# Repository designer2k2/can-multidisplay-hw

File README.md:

# can-multidisplay-hw
Displaying and measuring automotive related values, with CAN, GPS and more

Software: https://github.com/designer2k2/can-multidisplay

## Features:

* Teensy 4 Microcontroller https://www.pjrc.com/store/teensy40.html
* 12V -> 5V Power supply with TPS2113A voltage selector
* 3,3V Power supply
* RTC battery to support Teensy
* SD card slot, with flex cable to Teensy
* WS2812 level shifter 74AHCT1G125
* GPS serial port
* CAN transceiver SN65HVD232 with selectable 120Ohm resistor
* RS232 level shifter MAX3232
* MPU-6050  Six-Axis (Gyro + Accelerometer)
* I2C Levelshifter to 5V
* TMP75AIDR I2C Temperature sensor
* 4 channel 12Bit ADC ADS1015IDGS
* 6 protected inputs
* SSD1351 OLED  Interface
* ILI9341 + XPT2046 Touch display Interface

PCB is made in KiCad and parts selected to have it produced by JLCPCB

## Images:

PCB Backside:

3D Rendering with Display, GPS and RGB LED:

Display running:

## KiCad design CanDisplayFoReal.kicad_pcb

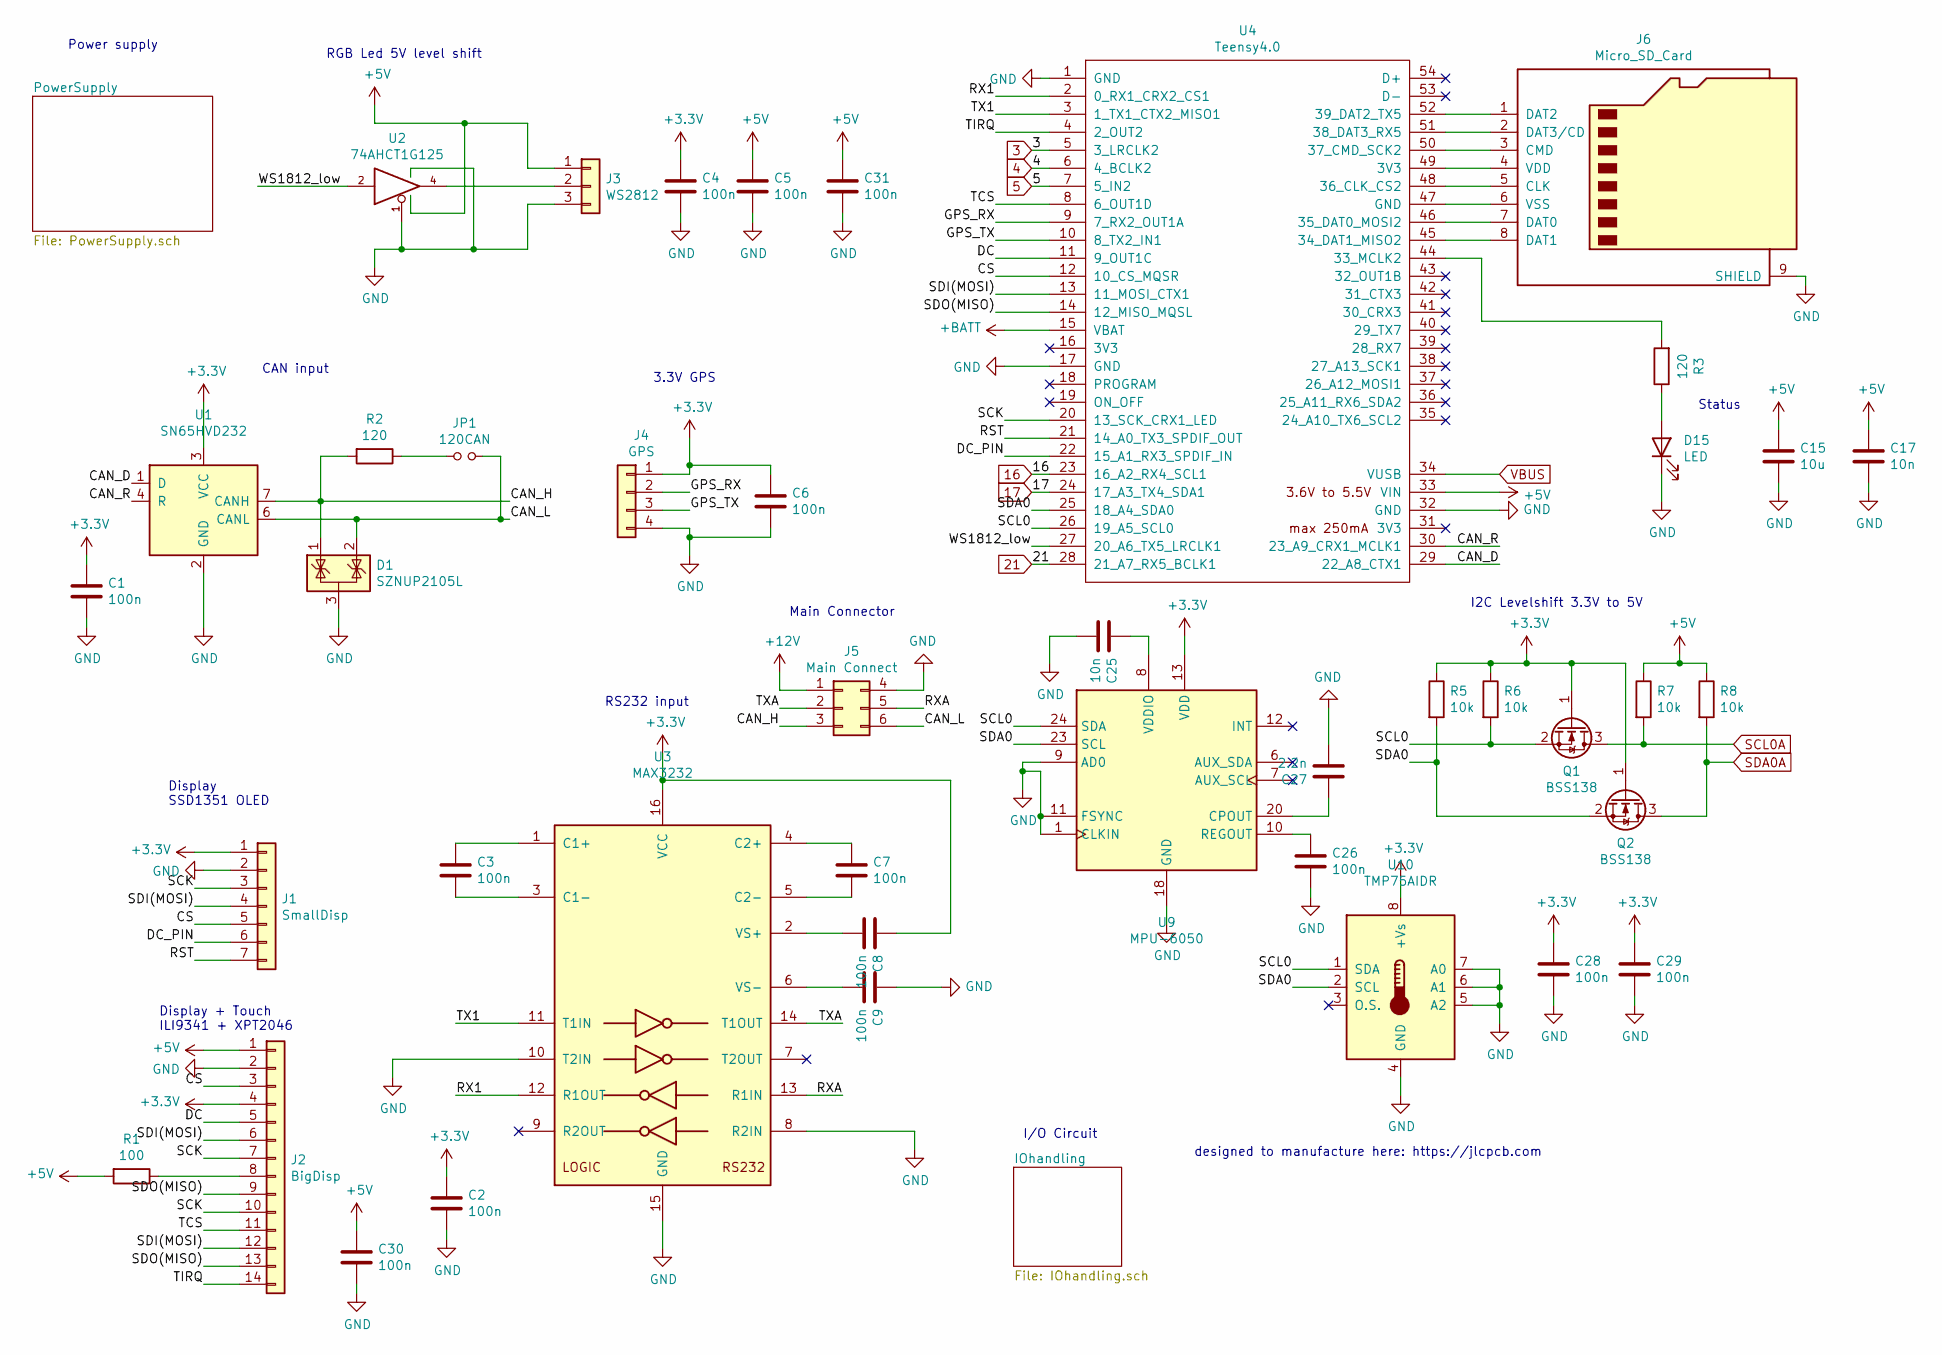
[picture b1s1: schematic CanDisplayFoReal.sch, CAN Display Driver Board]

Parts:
C1, C2, C3, C4, C5, C6, C7, C8, C9, C26, C28, C29, C30, C31: 100n; C_0603_1608Metric; JLCPCB C14663
C15: 10u; C_1206_3216Metric; JLCPCB C13585
C17, C25: 10n; C_0805_2012Metric; JLCPCB C1710
C27: 2.2n; C_0805_2012Metric; JLCPCB C28260
D1: SZNUP2105L; SOT-23; JLCPCB C233494
D15: LED; LED_0603_1608Metric; JLCPCB C2286
J1: SmallDisp; PinHeader_1x07_P2.54mm_Vertical
J2: BigDisp; PinHeader_1x14_P2.54mm_Vertical
J3: WS2812; PinHeader_1x03_P2.54mm_Vertical
J4: GPS; PinHeader_1x04_P2.54mm_Vertical
J5: Main Connect; Molex_Micro-Fit_3.0_43045-0612_2x03_P3.00mm_Vertical
J6: Micro_SD_Card; microSD_HC_Wuerth_693072010801
JP1: 120CAN; PinHeader_1x02_P2.54mm_Vertical
Q1, Q2: BSS138; SOT-23; JLCPCB C52895
R1: 100; R_0603_1608Metric; JLCPCB C22775
R2, R3: 120; R_0603_1608Metric; JLCPCB C22787
R5, R6, R7, R8: 10k; R_0603_1608Metric; JLCPCB C25804
U1: SN65HVD232; SOIC-8_3.9x4.9mm_P1.27mm; JLCPCB C30530
U2: 74AHCT1G125; SOT-23-5; JLCPCB C12494
U3: MAX3232; TSSOP-16_4.4x5mm_P0.65mm; JLCPCB C19767
U4: Teensy4.0; Teensy40_SMT
U9: MPU-6050; InvenSense_QFN-24_4x4mm_P0.5mm; JLCPCB C24112
U10: TMP75AIDR; SOIC-8_3.9x4.9mm_P1.27mm; JLCPCB C30389

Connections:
3: U4.5 (3_LRCLK2); also elsewhere on the board
4: U4.6 (4_BCLK2); also elsewhere on the board
5: U4.7 (5_IN2); also elsewhere on the board
16: U4.23 (16_A2_RX4_SCL1); also elsewhere on the board
17: U4.24 (17_A3_TX4_SDA1); also elsewhere on the board
21: U4.28 (21_A7_RX5_BCLK1); also elsewhere on the board
+3V3: C1.1, C2.1, C4.1, C6.1, C8.1, C28.1, C29.1, J1.1, J2.4, J4.1, Q1.1 (G), Q2.1 (G), R5.1, R6.1, U1.3 (VCC), U3.16 (VCC), U9.13 (VDD), U10.8 (+Vs); also elsewhere on the board
+5V: C5.1, C15.1, C17.1, C30.1, C31.1, J2.1, J3.1, R1.2, R7.1, R8.1, U2.5 (VCC), U4.33 (VIN); also elsewhere on the board
+12V: J5.1; also elsewhere on the board
+BATT: U4.15 (VBAT); also elsewhere on the board
/CAN_D: U1.1 (D), U4.29 (22_A8_CTX1)
/CAN_H: D1.1 (K), J5.3, R2.2, U1.7 (CANH)
/CAN_L: D1.2 (K), J5.6, JP1.2, U1.6 (CANL)
/CAN_R: U1.4 (R), U4.30 (23_A9_CRX1_MCLK1)
/CS: J1.5, J2.3, U4.12 (10_CS_MQSR)
/DC: J2.5, U4.11 (9_OUT1C)
/DC_PIN: J1.6, U4.22 (15_A1_RX3_SPDIF_IN)
/GPS_RX: J4.2, U4.9 (7_RX2_OUT1A)
/GPS_TX: J4.3, U4.10 (8_TX2_IN1)
/RST: J1.7, U4.21 (14_A0_TX3_SPDIF_OUT)
/RX1: U3.12 (R1OUT), U4.2 (0_RX1_CRX2_CS1)
/RXA: J5.5, U3.13 (R1IN)
/SCK: J1.3, J2.7, J2.10, U4.20 (13_SCK_CRX1_LED)
/SCL0: Q1.2 (S), R6.2, U4.26 (19_A5_SCL0), U9.24 (SDA), U10.1 (SDA)
/SDA0: Q2.2 (S), R5.2, U4.25 (18_A4_SDA0), U9.23 (SCL), U10.2 (SCL)
/SDI(MOSI): J1.4, J2.6, J2.12, U4.13 (11_MOSI_CTX1)
/SDO(MISO): J2.9, J2.13, U4.14 (12_MISO_MQSL)
/TCS: J2.11, U4.8 (6_OUT1D)
/TIRQ: J2.14, U4.4 (2_OUT2)
/TX1: U3.11 (T1IN), U4.3 (1_TX1_CTX2_MISO1)
/TXA: J5.2, U3.14 (T1OUT)
/WS1812_low: U2.2, U4.27 (20_A6_TX5_LRCLK1)
GND: C1.2, C2.2, C4.2, C5.2, C6.2, C9.1, C15.2, C17.2, C25.2, C26.2, C27.2, C28.2, C29.2, C30.2, C31.2, D1.3 (A), D15.1 (K), J1.2, J2.2, J3.3, J4.4, J5.4, J6.9 (SHIELD), U1.2 (GND), U2.1, U2.3 (GND), U3.8 (R2IN), U3.10 (T2IN), U3.15 (GND), U4.1 (GND), U4.17 (GND), U4.32 (GND), U9.1 (CLKIN), U9.9 (AD0), U9.11 (FSYNC), U9.18 (GND), U10.4 (GND), U10.5 (A2), U10.6 (A1), U10.7 (A0); also elsewhere on the board
unnamed: C3.1, U3.1 (C1+)
unnamed: C3.2, U3.3 (C1-)
unnamed: C7.1, U3.4 (C2+)
unnamed: C7.2, U3.5 (C2-)
unnamed: C8.2, U3.2 (VS+)
unnamed: C9.2, U3.6 (VS-)
unnamed: C25.1, U9.8 (VDDIO)
unnamed: C26.1, U9.10 (REGOUT)
unnamed: C27.1, U9.20 (CPOUT)
unnamed: D15.2 (A), R3.1
unnamed: J2.8, R1.1
unnamed: J3.2, U2.4
unnamed: J6.1 (DAT2), U4.52 (39_DAT2_TX5)
unnamed: J6.2 (DAT3/CD), U4.51 (38_DAT3_RX5)
unnamed: J6.3 (CMD), U4.50 (37_CMD_SCK2)
unnamed: J6.4 (VDD), U4.49 (3V3)
unnamed: J6.5 (CLK), U4.48 (36_CLK_CS2)
unnamed: J6.6 (VSS), U4.47 (GND)
unnamed: J6.7 (DAT0), U4.46 (35_DAT0_MOSI2)
unnamed: J6.8 (DAT1), U4.45 (34_DAT1_MISO2)
unnamed: JP1.1, R2.1
unnamed: R3.2, U4.44 (33_MCLK2)
SCL0A: Q1.3 (D), R7.2; also elsewhere on the board
SDA0A: Q2.3 (D), R8.2; also elsewhere on the board
VBUS: U4.34 (VUSB); also elsewhere on the board

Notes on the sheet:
designed to manufacture here: https://jlcpcb.com
Display SSD1351 OLED
RGB Led 5V level shift
CAN input
3.3V GPS
RS232 input
Power supply
I2C Levelshift 3.3V to 5V
Main Connector
I/O Circuit
Display + Touch ILI9341 + XPT2046
Status

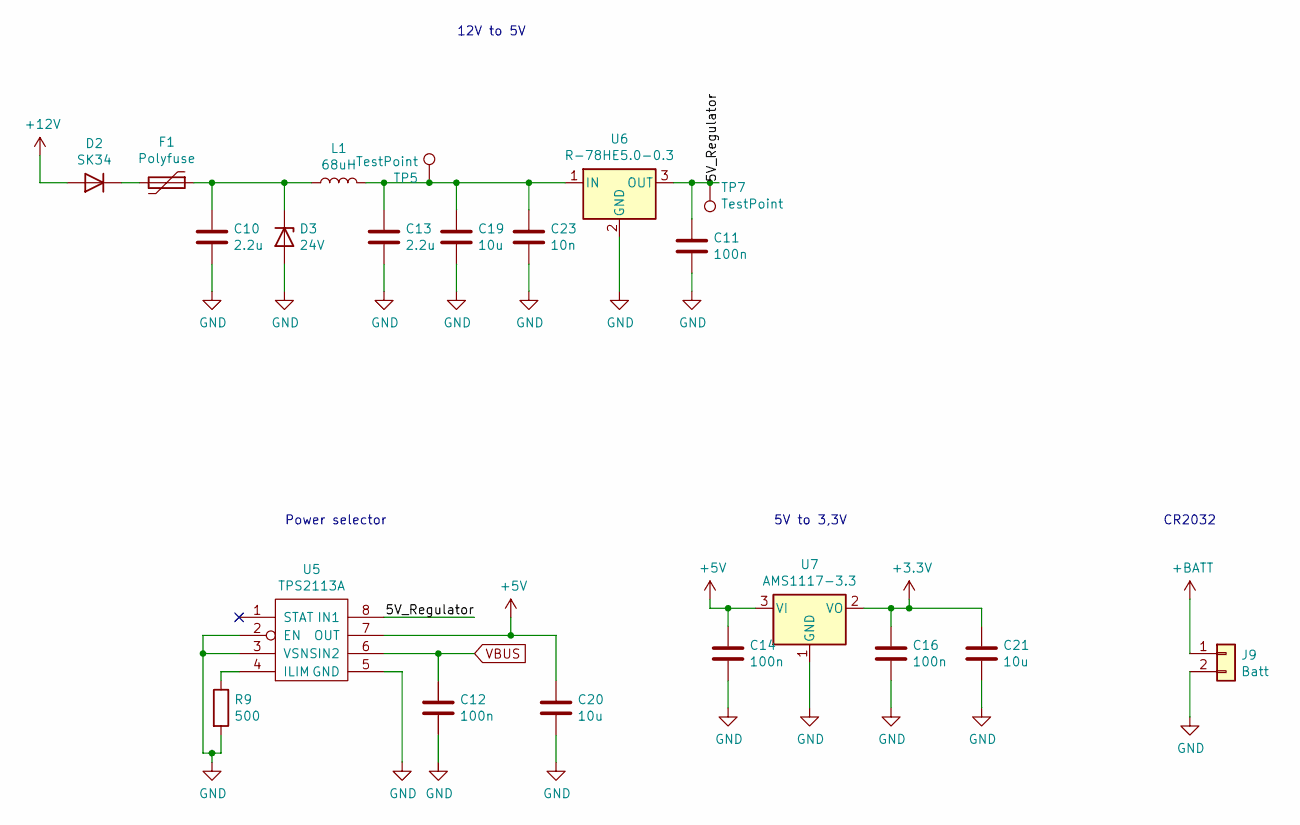
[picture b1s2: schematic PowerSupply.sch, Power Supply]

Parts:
C10, C13: 2.2u; C_0805_2012Metric; JLCPCB C49217
C11, C12, C14, C16: 100n; C_0603_1608Metric; JLCPCB C14663
C19, C20, C21: 10u; C_1206_3216Metric; JLCPCB C13585
C23: 10n; C_0805_2012Metric; JLCPCB C1710
D2: SK34; D_SMA; JLCPCB C65008
D3: 24V; D_SOD-323; JLCPCB C463816
F1: Polyfuse; Fuse_1206_3216Metric_Castellated; JLCPCB C70082
J9: Batt; PinHeader_1x02_P2.54mm_Vertical
L1: 68uH; L_6.3x6.3_H3; JLCPCB C86662
R9: 500; R_0603_1608Metric; JLCPCB C22808
TP5, TP7: TestPoint; TestPoint_Pad_D2.0mm
U5: TPS2113A; TSSOP-8_4.4x3mm_P0.65mm; JLCPCB C130052
U6: R-78HE5.0-0.3; Converter_DCDC_RECOM_R-78E-0.5_THT
U7: AMS1117-3.3; SOT-223-3_TabPin2; JLCPCB C6186

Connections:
+3V3: C16.1, C21.1, U7.2 (VO); also elsewhere on the board
+5V: C14.1, C20.1, U5.7 (OUT), U7.3 (VI); also elsewhere on the board
+12V: D2.2 (A); also elsewhere on the board
+BATT: J9.1; also elsewhere on the board
/PowerSupply/5V_Regulator: C11.1, TP7.1, U5.8 (IN1), U6.3 (OUT)
GND: C10.2, C11.2, C12.2, C13.2, C14.2, C16.2, C19.2, C20.2, C21.2, C23.2, D3.2 (A), J9.2, R9.2, U5.2 (EN), U5.3 (VSNS), U5.5 (GND), U6.2 (GND), U7.1 (GND); also elsewhere on the board
unnamed: C10.1, D3.1 (K), F1.1, L1.1
unnamed: C13.1, C19.1, C23.1, L1.2, TP5.1, U6.1 (IN)
unnamed: D2.1 (K), F1.2
unnamed: R9.1, U5.4 (ILIM)
VBUS: C12.1, U5.6 (IN2); also elsewhere on the board

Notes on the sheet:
12V to 5V
Power selector
5V to 3,3V
CR2032

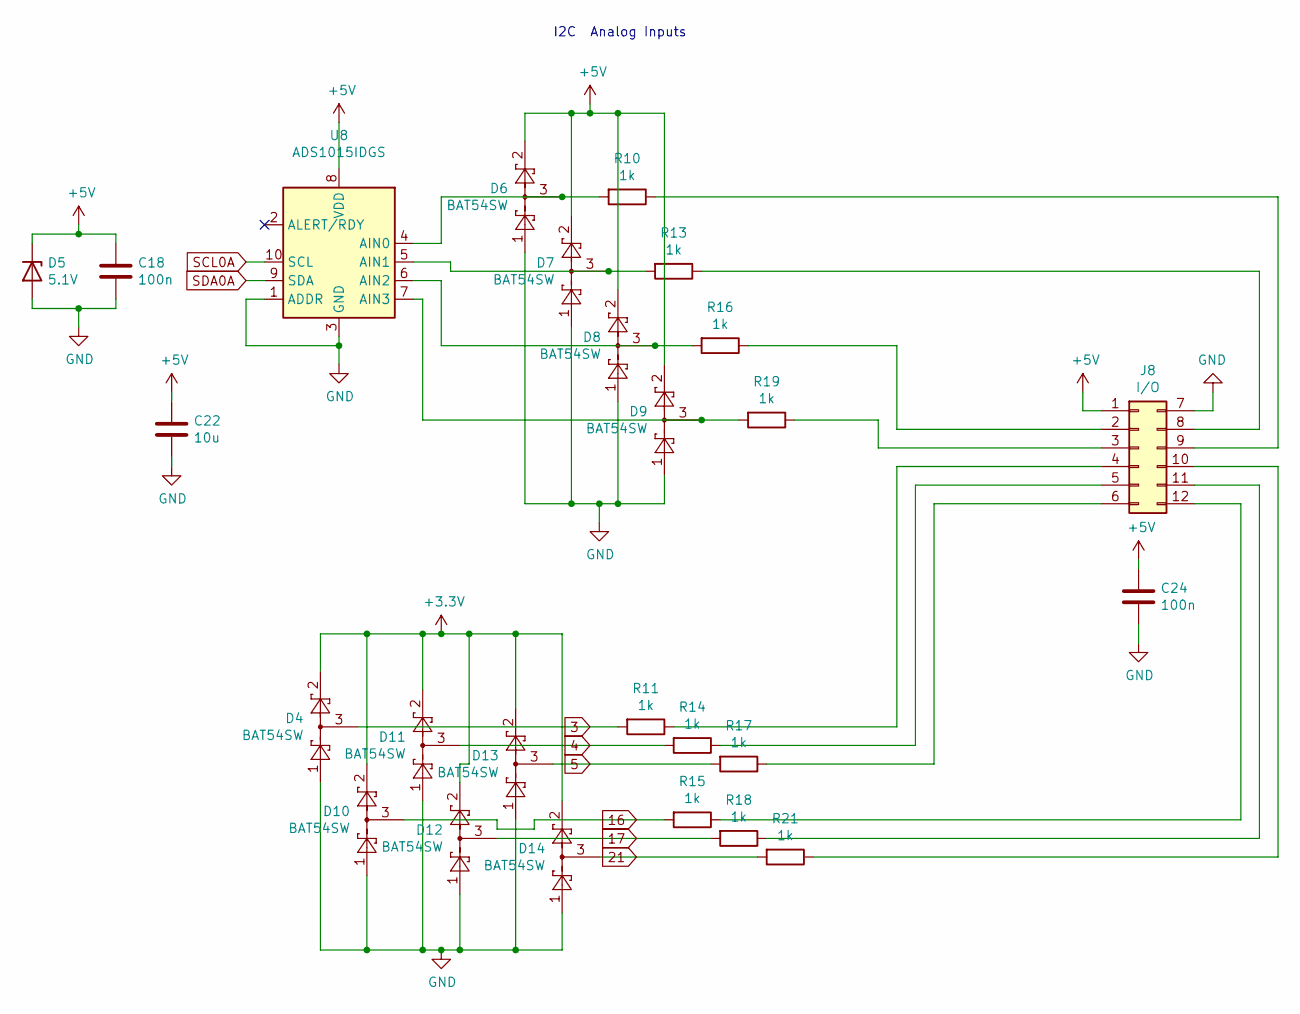
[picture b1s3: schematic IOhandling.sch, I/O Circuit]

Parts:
C18, C24: 100n; C_0603_1608Metric; JLCPCB C14663
C22: 10u; C_1206_3216Metric; JLCPCB C13585
D4, D6, D7, D8, D9, D10, D11, D12, D13, D14: BAT54SW; SOT-323_SC-70; JLCPCB C78260
D5: 5.1V; D_SOD-323; JLCPCB C85392
J8: I/O; Molex_Micro-Fit_3.0_43045-1212_2x06_P3.00mm_Vertical
R10, R11, R13, R14, R15, R16, R17, R18, R19, R21: 1k; R_0603_1608Metric; JLCPCB C21190
U8: ADS1015IDGS; TSSOP-10_3x3mm_P0.5mm; JLCPCB C193969

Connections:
3: D4.3, R11.2; also elsewhere on the board
4: D11.3, R14.2; also elsewhere on the board
5: D13.3, R17.2; also elsewhere on the board
16: D10.3, R15.2; also elsewhere on the board
17: D12.3, R18.2; also elsewhere on the board
21: D14.3, R21.2; also elsewhere on the board
+3V3: D4.2, D10.2, D11.2, D12.2, D13.2, D14.2; also elsewhere on the board
+5V: C18.1, C22.1, C24.1, D5.1 (K), D6.2, D7.2, D8.2, D9.2, J8.1, U8.8 (VDD); also elsewhere on the board
GND: C18.2, C22.2, C24.2, D4.1, D5.2 (A), D6.1, D7.1, D8.1, D9.1, D10.1, D11.1, D12.1, D13.1, D14.1, J8.7, U8.1 (ADDR), U8.3 (GND); also elsewhere on the board
unnamed: D6.3, R10.2, U8.4 (AIN0)
unnamed: D7.3, R13.2, U8.5 (AIN1)
unnamed: D8.3, R16.2, U8.6 (AIN2)
unnamed: D9.3, R19.2, U8.7 (AIN3)
unnamed: J8.2, R16.1
unnamed: J8.3, R19.1
unnamed: J8.4, R11.1
unnamed: J8.5, R14.1
unnamed: J8.6, R17.1
unnamed: J8.8, R13.1
unnamed: J8.9, R10.1
unnamed: J8.10, R21.1
unnamed: J8.11, R18.1
unnamed: J8.12, R15.1
SCL0A: U8.10 (SCL); also elsewhere on the board
SDA0A: U8.9 (SDA); also elsewhere on the board

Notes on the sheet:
I2C Analog Inputs

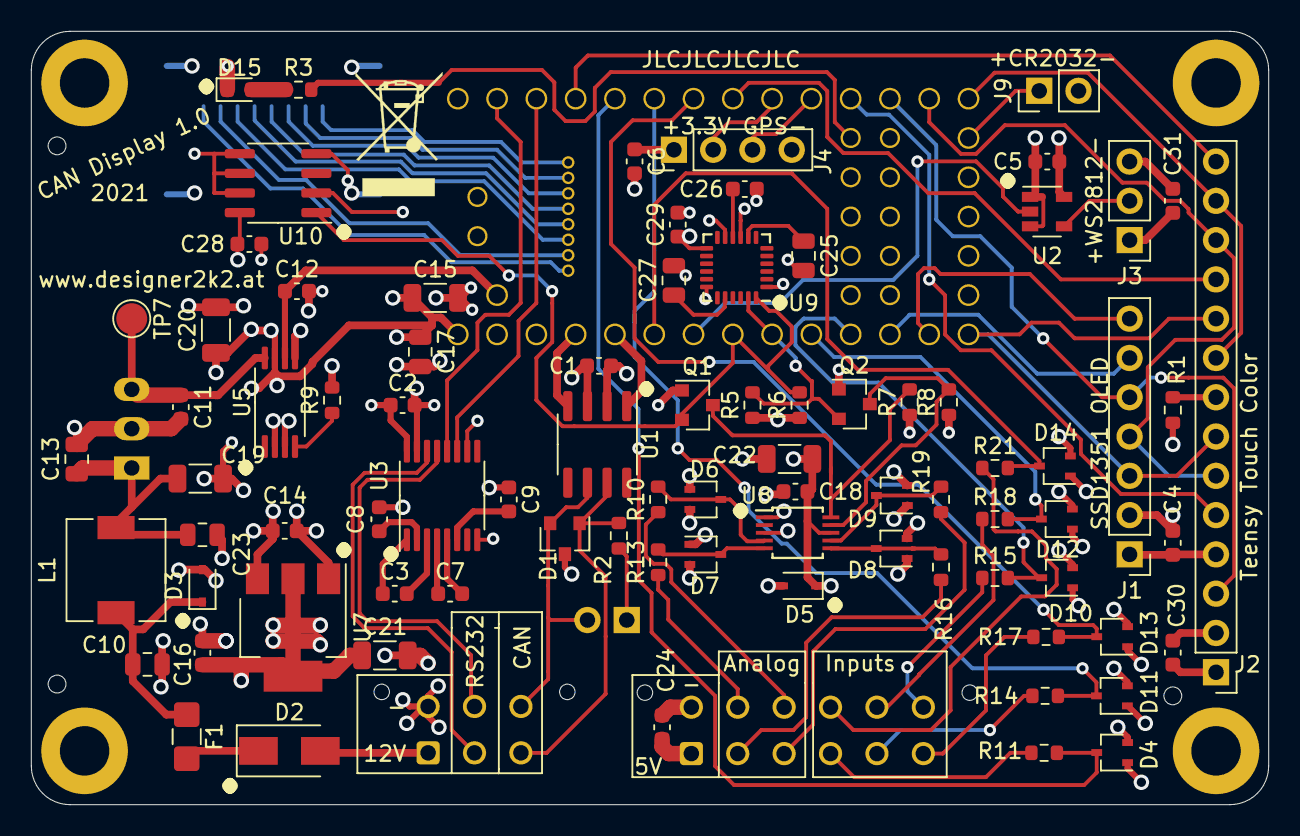
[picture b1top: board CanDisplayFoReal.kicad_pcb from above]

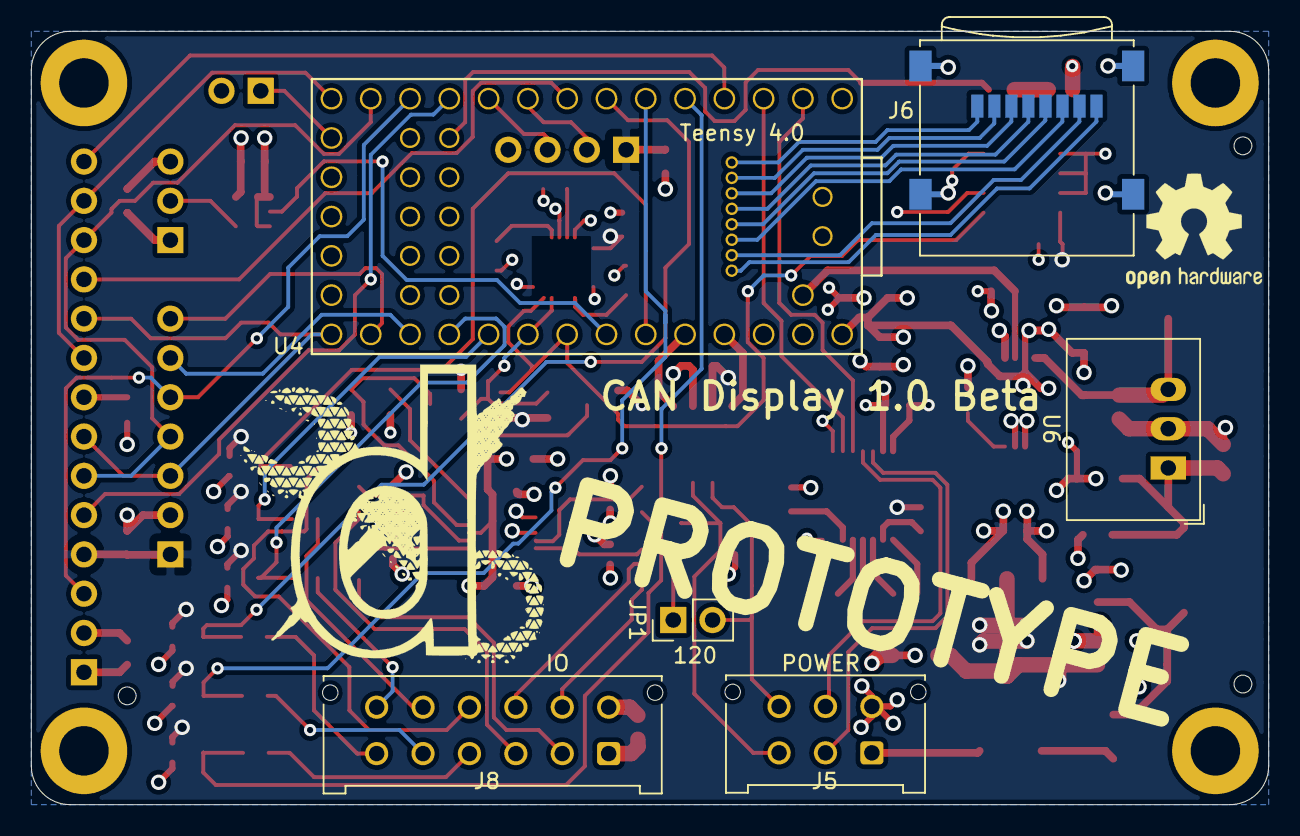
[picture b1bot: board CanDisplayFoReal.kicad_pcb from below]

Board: 4 copper layers, 80.0 x 50.0 mm, 88 parts (6 on the bottom side), 77 nets.

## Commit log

2021-08-10 initial hardware
    hardware as it was ordered
2021-08-10 add ibom
    interactive BOM
2021-08-10 add BOM
    BOM used for ordering the pcb´s
2021-08-11 add Schematic pdf
2021-08-16 add images
2021-08-20 Create License
